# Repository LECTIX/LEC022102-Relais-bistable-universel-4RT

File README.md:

# LEC022102 - Relais bistable universel 12V 4RT
Fichiers sources pour le produit LEC022102

## Description du produit

Ce module est un relais bistable disposant de toutes les protections nécessaires pour être utilisé avec une tension de 12 à 16 V alternative ou continue.
Comme tous les relais bistable, une seule impulsion est nécessaire pour faire basculer les contacts inverseurs d'un côté ou de l'autre, ce qui le rend idéal pour être utilisé avec des ILS ou bien des boutons poussoirs.
- **ALIMENTATION** 12 – 16 V AC / DC.
- **4 CONTACTS INVERSEURS** indépendants (2 x DPDT).
- **FAIBLE CONSOMMATION** de 30 mA lorsqu'une des bobines relais est alimentée.
- **POUVOIR DE COUPURE** de 2A.

## Applications

- Cantonnement analogique
- Zone de protection faller car system
- Boucle de retournement
- Extension de contact inverseurs (aiguillages, relais, interrupteurs, …)
- Gestion d'un passage à niveau

## Installation

L’installation est simple et rapide :

1. Brancher le commun au pole négatif de l'alimentation.
1. Pour chacune des bornes R et S, intercaller un interrupteur ou équivalent (ILS, pédale, capteur Hall, contact inverseur, …) entre la borne et le pole positif de l'alimentation.
1. Les contacts inverseurs du relais réagissent en fonction du bouton sur lequel on appui.

**Attention** : Il ne faut en aucun cas alimenter les 2 bornes R et S simultanément.

## Utiliser les fichiers sources pour fabriquer le produit

Il n'est **pas nécessaire de savoir souder ou d'être bon en électronique** pour se procurer ce produit. Grâce aux fichiers sources publiés ici, vous pouvez être en mesure de faire fabriquer ce produit par un sous traitant.

### Faire fabriquer chez un sous traitant

Il est aujourd'hui possible de faire fabriquer à moindre cout des cartes électroniques. Nous recommendons [JLCPCB](https://jlcpcb.com/) si vous voulez aller au moins cher. Si vous préférez un acteur européen, [eurocircuits](https://www.eurocircuits.com/) est un des acteurs reconnus.

1. Télécherger les sources de ce produit en cliquant sur le bouton `Code`, puis `Download ZIP`.
1. Décompresser le dossier.
1. Les fichiers pour la fabrication se trouvent dans le répertoire `hardware/prod`.
1. Se connecter sur [https://cart.jlcpcb.com/quote](https://cart.jlcpcb.com/quote)
1. Cliquer sur le bouton `Add gerber file` et sélectionner le fichier `gerbers.zip`.
1. Sélectionnez la quantité de cartes que vous souhaitez dans le champs `PCB Qty`.
1. Laisser toutes les autres options par défaut, puis cliquez sur le toggle switch en face de `PCB Assembly`, et enfin sur le bouton `confirm`.
1. Une preview de la carte électronique sans les composants doit apparaitre. Cliquez sur `NEXT`.
1. Cliquez sur le bouton `Add BOM File`, puis sélectionnez le fichier `bom.csv`
1. Cliquez sur le bouton `Add CPL File`, puis sélectionnez le fichier `pos.csv`
1. **Vérifier que tous les composants sont en stock** et bien sélectionnés, puis cliquez sur `NEXT`.
1. Une preview de la carte avec ses composants apparait. Continuer le chemin en cliquant sur `NEXT`.
1. Le prix final apparait. Sélectionnez la catégorie du produit, puis cliquez sur `SAVE TO CART`.
1. Une fois sauvegardé dans votre panier, vous pouvez valider votre commande et choisir le moyen d'acheminement. Afin de ne pas avoir à se préoccuper des frais de douane, nous vous conseillons de choisir une méthode d'expédition DDP.

Vous receverez vos cartes sous 1 à 3 semaines. 

**Nous ne sommes en aucun cas responsables des cartes qui arriveraient défectueuses ou non fonctionnelles.**

### Modifications des fichiers sources

Installez kicad 6 (ou version supérieure), et ouvrez le fichier LEC022102.kicad_pro

### Regénérer les fichiers gerber, BOM, et position (Optionnel)

Peut se faire simplement en utilisant kikit :

```
cd hardware

# generate assembly files
docker run --rm -w /kikit -v $PWD:/kikit yaqwsx/kikit kikit fab jlcpcb --assembly --no-drc --schematic LEC022102.kicad_sch --field LCSC --corrections JLCPCB_CORRECTION --nametemplate LEC022102_{} LEC022102.kicad_pcb prod/

```

## License
Tous nos fichiers sont plubliés sous la license CERN Open Hardware Licence Version 2 - Strongly Reciprocal

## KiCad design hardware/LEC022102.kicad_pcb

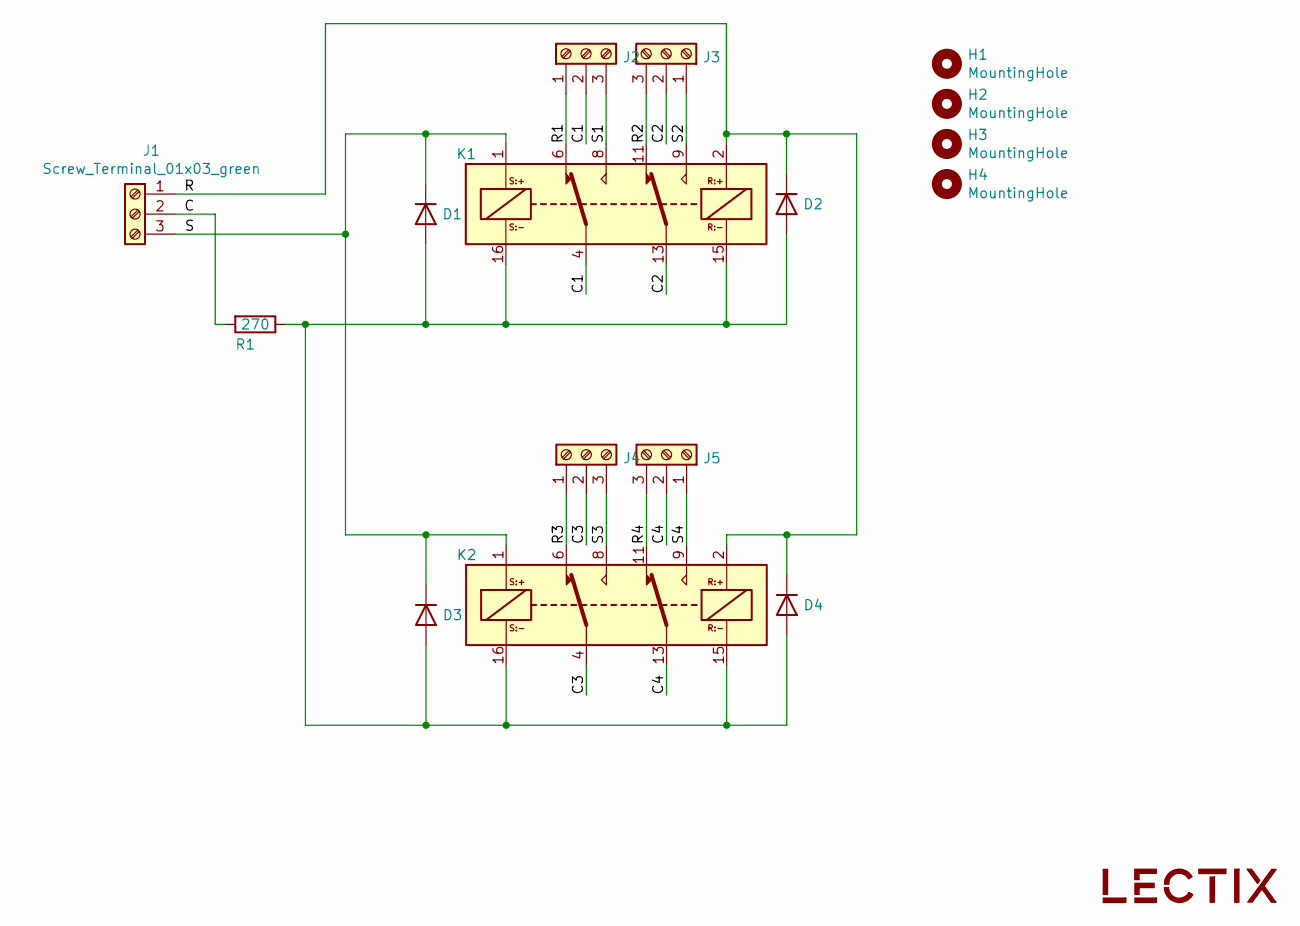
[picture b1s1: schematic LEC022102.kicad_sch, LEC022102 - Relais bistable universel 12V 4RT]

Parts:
D1, D2, D3, D4: 1N4148W; D_SOD-123; LCSC C81598
H1, H2, H3, H4: MountingHole; MountingHole_3.2mm_M3; JLCPCB BOM 0
J1: Screw_Terminal_01x03_green; TerminalBlock_bornier-3_P5.08mm-green; MPN DB126V-5.0-3P-GN; LCSC C395850
J2, J3, J4, J5: Screw_Terminal_01x03_blue; TerminalBlock_bornier-3_P5.08mm-blue; MPN DB301V-5.0-3P-BU-P; LCSC C430620
K1, K2: HFD2-012-M-L2; Relay_DPDT_HFD2-xxx-M-L2; LCSC C399484
LOGO1: logo_lectix_25mm; Logo_10mm; JLCPCB BOM 0
R1: 270; R_0805_2012Metric; LCSC C17590

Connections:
/C: J1.2, R1.2
/C1: J2.2, K1.4
/C2: J3.2, K1.13
/C3: J4.2, K2.4
/C4: J5.2, K2.13
/R: D2.1 (K), D4.1 (K), J1.1, K1.2, K2.2
/R1: J2.1, K1.6
/R2: J3.3, K1.11
/R3: J4.1, K2.6
/R4: J5.3, K2.11
/S: D1.1 (K), D3.1 (K), J1.3, K1.1, K2.1
/S1: J2.3, K1.8
/S2: J3.1, K1.9
/S3: J4.3, K2.8
/S4: J5.1, K2.9
unnamed: D1.2 (A), D2.2 (A), D3.2 (A), D4.2 (A), K1.15, K1.16, K2.15, K2.16, R1.1

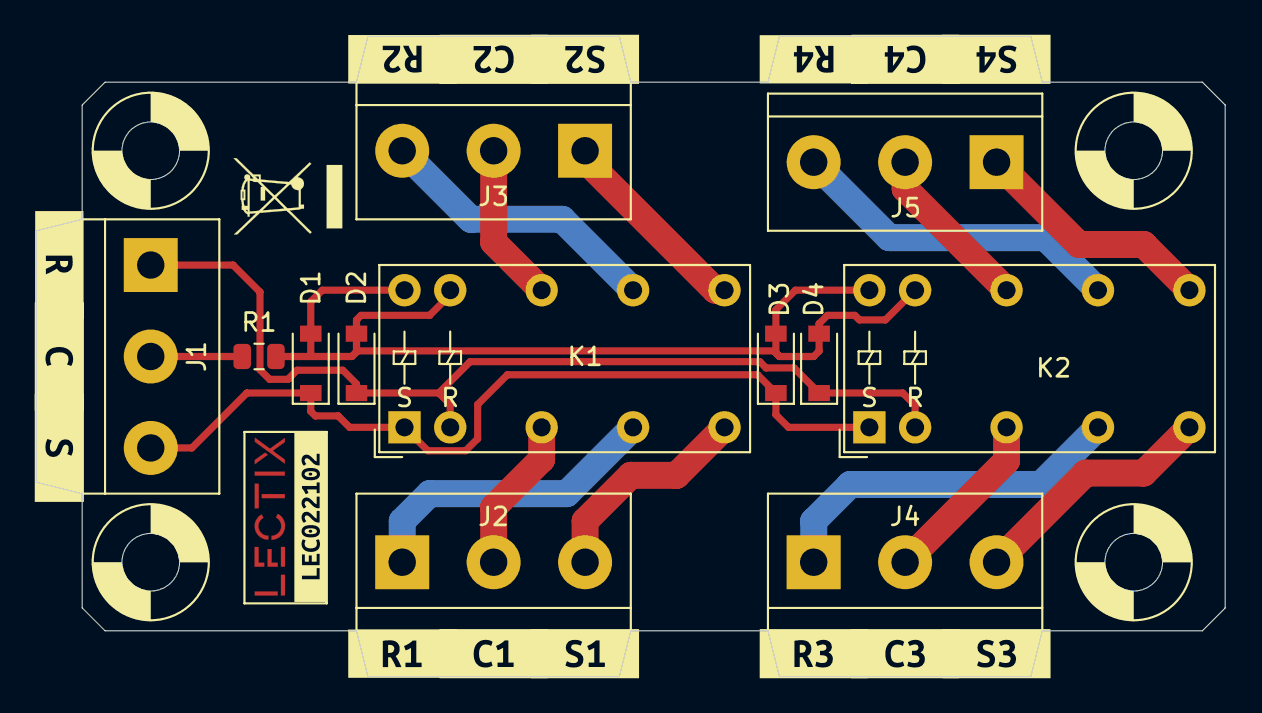
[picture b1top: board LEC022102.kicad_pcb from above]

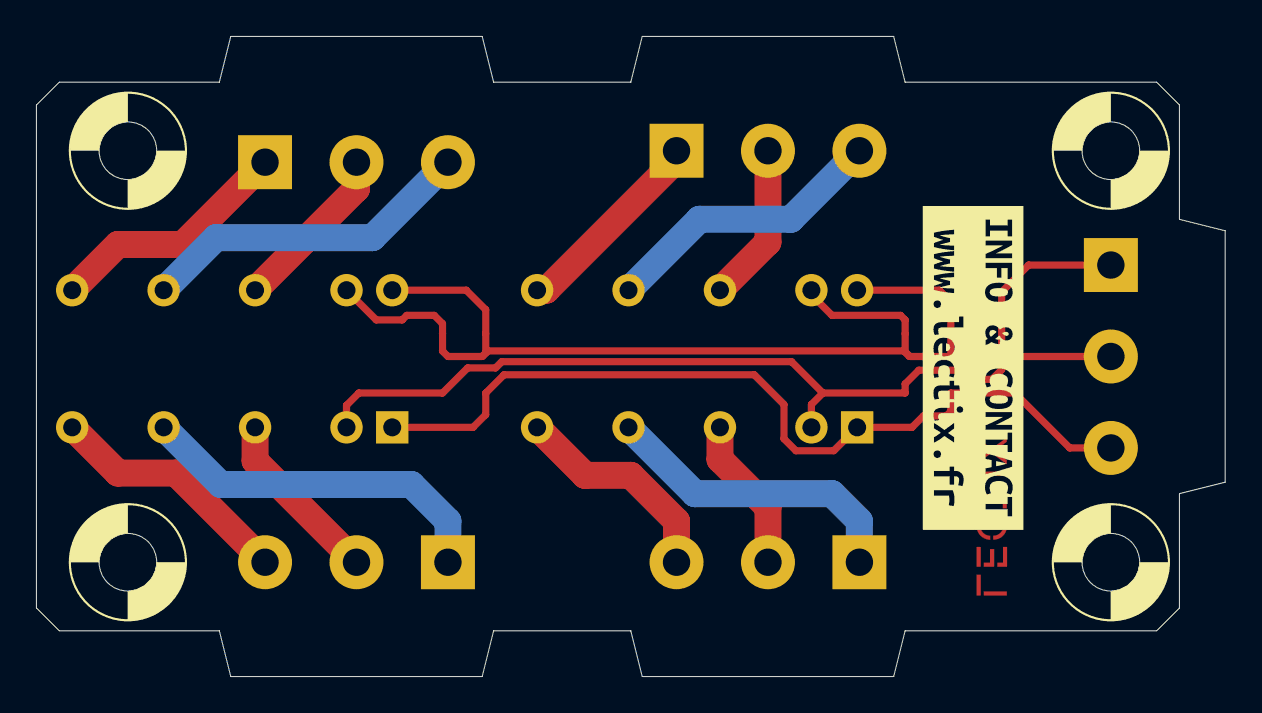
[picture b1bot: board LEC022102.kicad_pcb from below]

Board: 2 copper layers, 66.0 x 35.6 mm, 35 parts (2 on the bottom side), 16 nets.

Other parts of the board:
kibuzzard-62BC6D4A: G***; kibuzzard-62BC6D4A
kibuzzard-62BC6E53: G***; kibuzzard-62BC6E53
kibuzzard-62BC6E84: G***; kibuzzard-62BC6E84
kibuzzard-62BC6E90: G***; kibuzzard-62BC6E90
kibuzzard-62BC6EEB: G***; kibuzzard-62BC6EEB
kibuzzard-62BC6EF6: G***; kibuzzard-62BC6EF6
kibuzzard-62BC6EFE: G***; kibuzzard-62BC6EFE
kibuzzard-62BC6F2E: G***; kibuzzard-62BC6F2E
kibuzzard-62BC6F5D: G***; kibuzzard-62BC6F5D
kibuzzard-62BC6F34: G***; kibuzzard-62BC6F34
kibuzzard-62BC6F39: G***; kibuzzard-62BC6F39
kibuzzard-62BC6F64: G***; kibuzzard-62BC6F64
kibuzzard-62BC6F69: G***; kibuzzard-62BC6F69
kibuzzard-62BC6F76: G***; kibuzzard-62BC6F76
kibuzzard-62BC6F83: G***; kibuzzard-62BC6F83
kibuzzard-62BC6F89: G***; kibuzzard-62BC6F89
kibuzzard-62BCA36B: G***; kibuzzard-62BCA36B
kibuzzard-62BCA378: G***; kibuzzard-62BCA378

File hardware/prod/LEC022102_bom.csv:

Comment,Designator,Footprint,LCSC
1N4148W,"D1,D2,D3,D4",Diode_SMD:D_SOD-123,C81598
Screw_Terminal_01x03_green,J1,0_connectors:TerminalBlock_bornier-3_P5.08mm-green,C395850
Screw_Terminal_01x03_blue,"J2,J3,J4,J5",0_connectors:TerminalBlock_bornier-3_P5.08mm-blue,C430620
HFD2-012-M-L2,"K1,K2",0_relays:Relay_DPDT_HFD2-xxx-M-L2,C399484
270,R1,Resistor_SMD:R_0805_2012Metric,C17590

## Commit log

2023-04-19 Add hardware source files
